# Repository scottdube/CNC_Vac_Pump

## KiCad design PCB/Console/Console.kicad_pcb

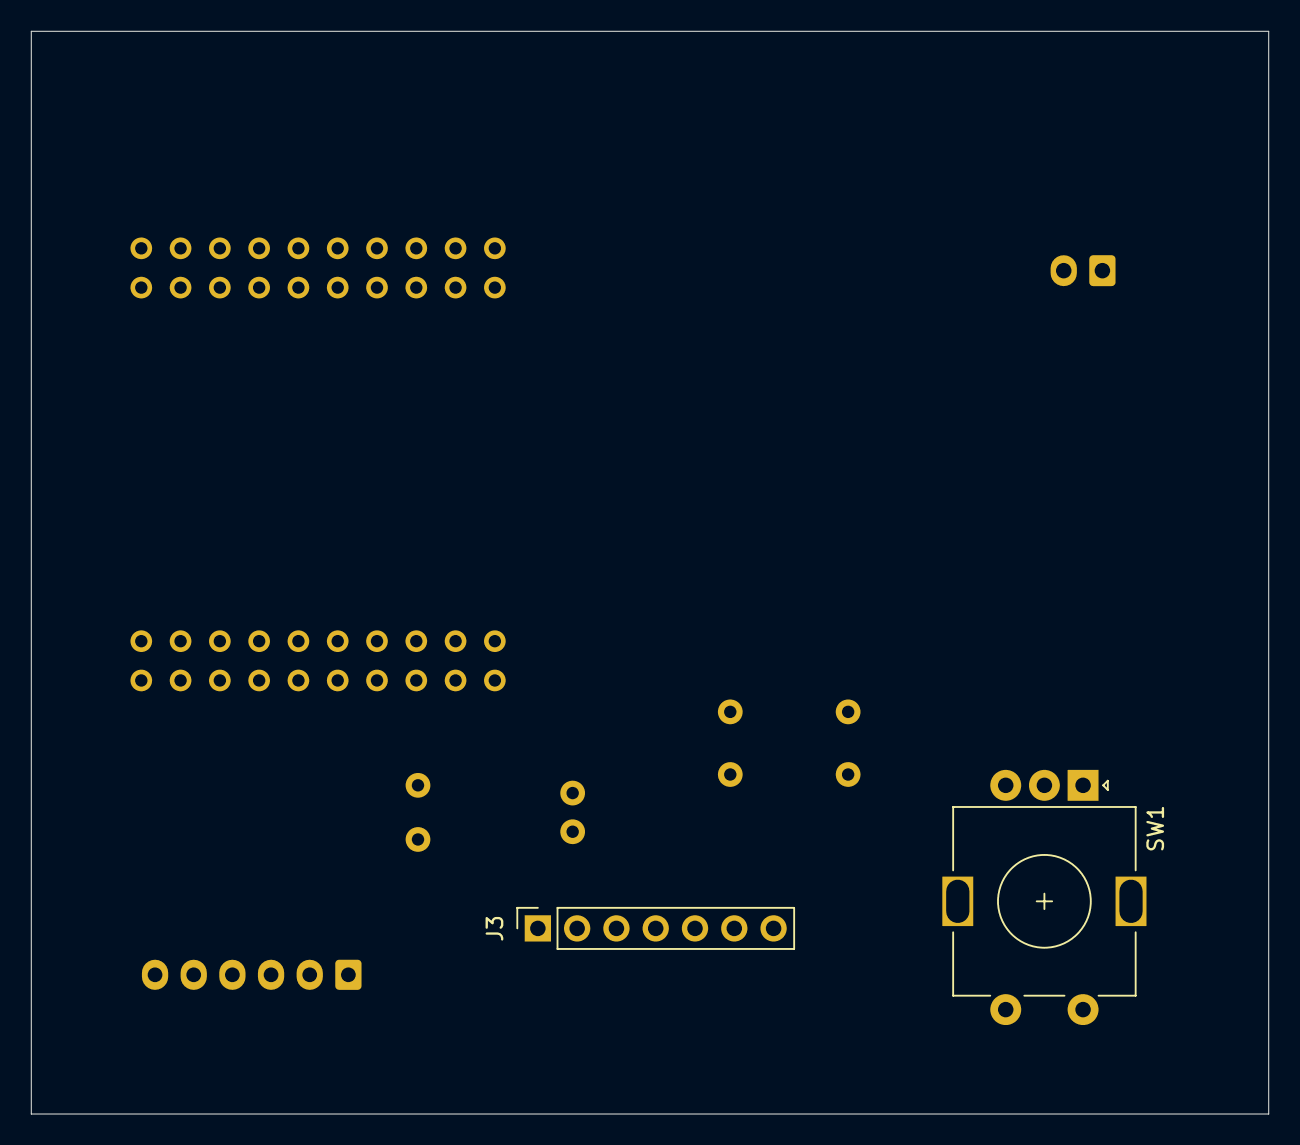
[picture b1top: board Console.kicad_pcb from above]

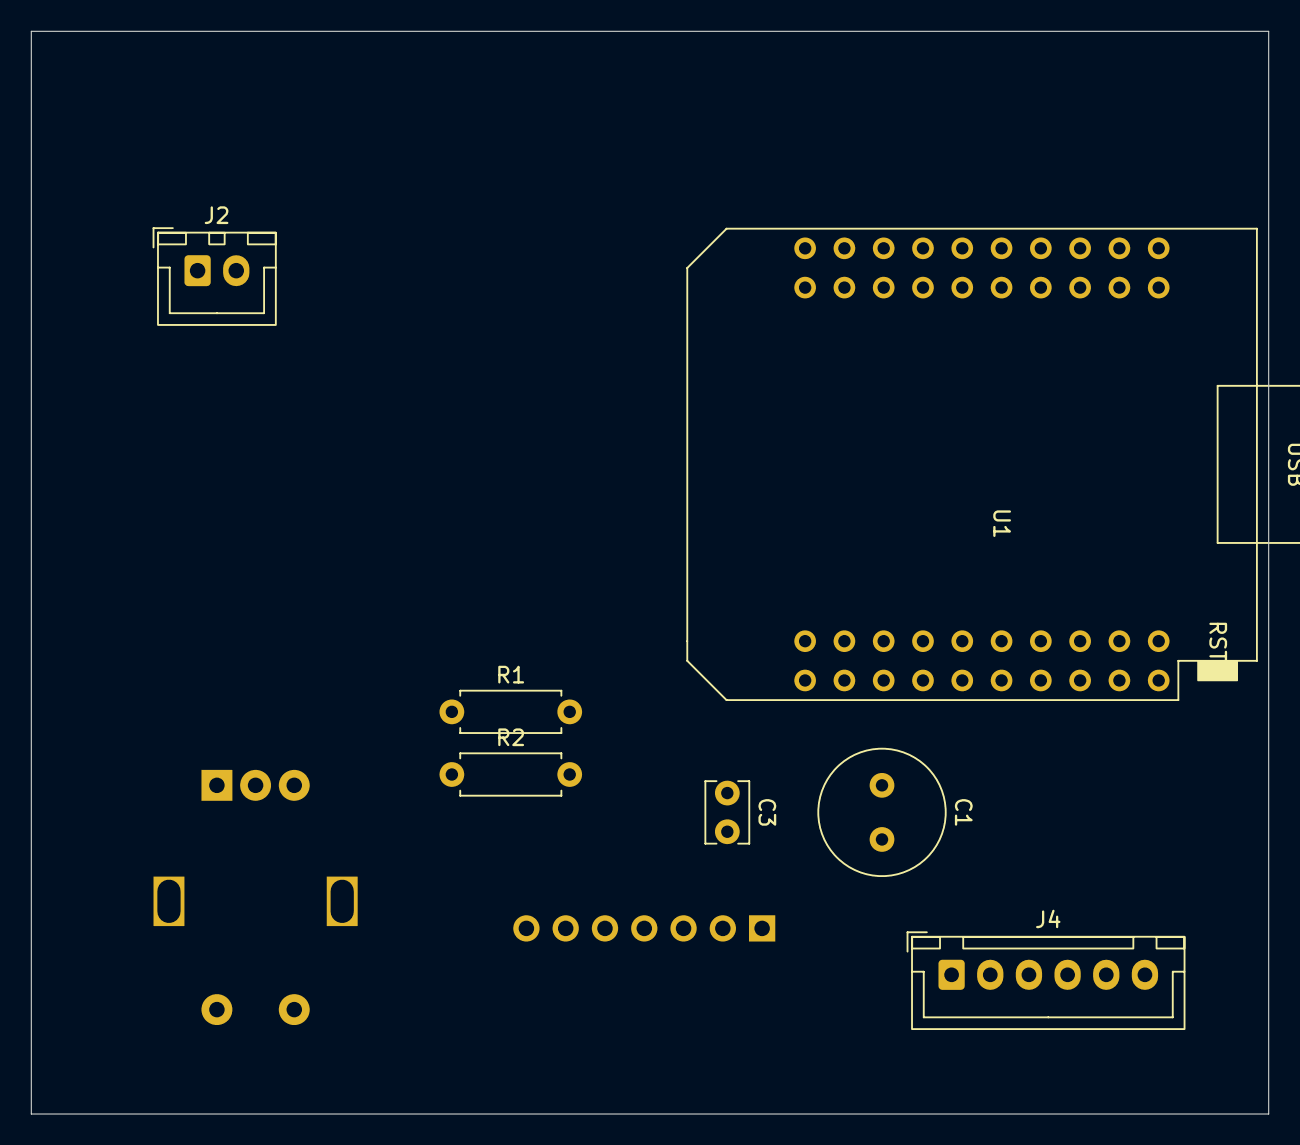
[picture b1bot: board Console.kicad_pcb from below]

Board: 2 copper layers, 80.0 x 70.0 mm, 9 parts (7 on the bottom side), 16 nets, no tracks yet.

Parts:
C1: 10uF; C_Radial_D8.0mm_H11.5mm_P3.50mm
C3: 100pF; C_Disc_D3.8mm_W2.6mm_P2.50mm
J2: Conn_01x02_Socket; JST_XH_B2B-XH-A_1x02_P2.50mm_Vertical
J3: Conn_01x07; PinSocket_1x07_P2.54mm_Vertical
J4: Conn_01x06; JST_XH_B6B-XH-A_1x06_P2.50mm_Vertical
R1: 5k; R_Axial_DIN0207_L6.3mm_D2.5mm_P7.62mm_Horizontal
R2: 10k; R_Axial_DIN0207_L6.3mm_D2.5mm_P7.62mm_Horizontal
SW1: RotaryEncoder_Switch_MP; RotaryEncoder_Alps_EC11E-Switch_Vertical_H20mm
U1: WeMos D1 Mini32; ESP32_mini

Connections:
/5Vdc: J2.1, J4.1
/5Vdc_switched: J2.2, U1.16 (Vcc)
/Alarm: J4.6, U1.30 (IO33)
/ENC_ChanA: SW1.A, U1.5 (IO25)
/ENC_ChanB: SW1.B, U1.7 (IO32)
/ENC_PB: SW1.S1, U1.3 (IO27)
/LCD_CS: J3.6, U1.33 (IO5)
/LCD_DC: J3.5, U1.10 (IO17)
/LCD_MOSI: J3.4, U1.31 (IO23)
/LCD_RST: J3.7, U1.12 (IO16)
/LCD_SClk: J3.3, U1.27 (IO18)
/LCD_Vcc: J3.1, U1.35 (3.3v)
/Vac_Pump: J4.5, U1.25 (IO26)
/Vac_Sensor: C1.1, C3.1, J4.3, R1.1
/Vacuum_Sig: R1.2, R2.1, U1.28 (IO35)
GND: C1.2, C3.2, J3.2, J4.2, J4.4, R2.2, SW1.C, SW1.MP, SW1.S2, U1.1 (Gnd), U1.14 (GND), U1.22 (GND)
